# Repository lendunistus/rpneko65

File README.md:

# RPNeko65

**This branch contains the work-in-progress second revision. NOTHING HERE IS CONFIRMED WORKING!**

An open source multi-layout PCB for the [Bakeneko65](https://github.com/kkatano/bakeneko-65)

## Features
- QMK/VIA
- RGB LED under Caps Lock (currently non-functional without modification)
- Large amount of layout support
- C3 Unified Daughterboard
- Support for clip-in stabilizers

## Layout support

## Release history
- Rev 1: Initial prototype. Caps Lock LED is non-functional due to incorrect capacitor wiring, can be fixed by removing the capacitor and bridging the two pads. ANSI enter and spacebar stabiliser holes are also misaligned

## Credits
- kkatano for creating the original Bakeneko65
- Zykrah for their [firmware script](https://github.com/zykrah/firmware-scripts)
- MarvFPV and ebastler for [marbastlib](https://github.com/ebastler/marbastlib)
- Sleepdealer for their [RP2040 design guide](https://github.com/Sleepdealr/RP2040-designguide)
- People in the Keyboard Atelier server for the help and assistance

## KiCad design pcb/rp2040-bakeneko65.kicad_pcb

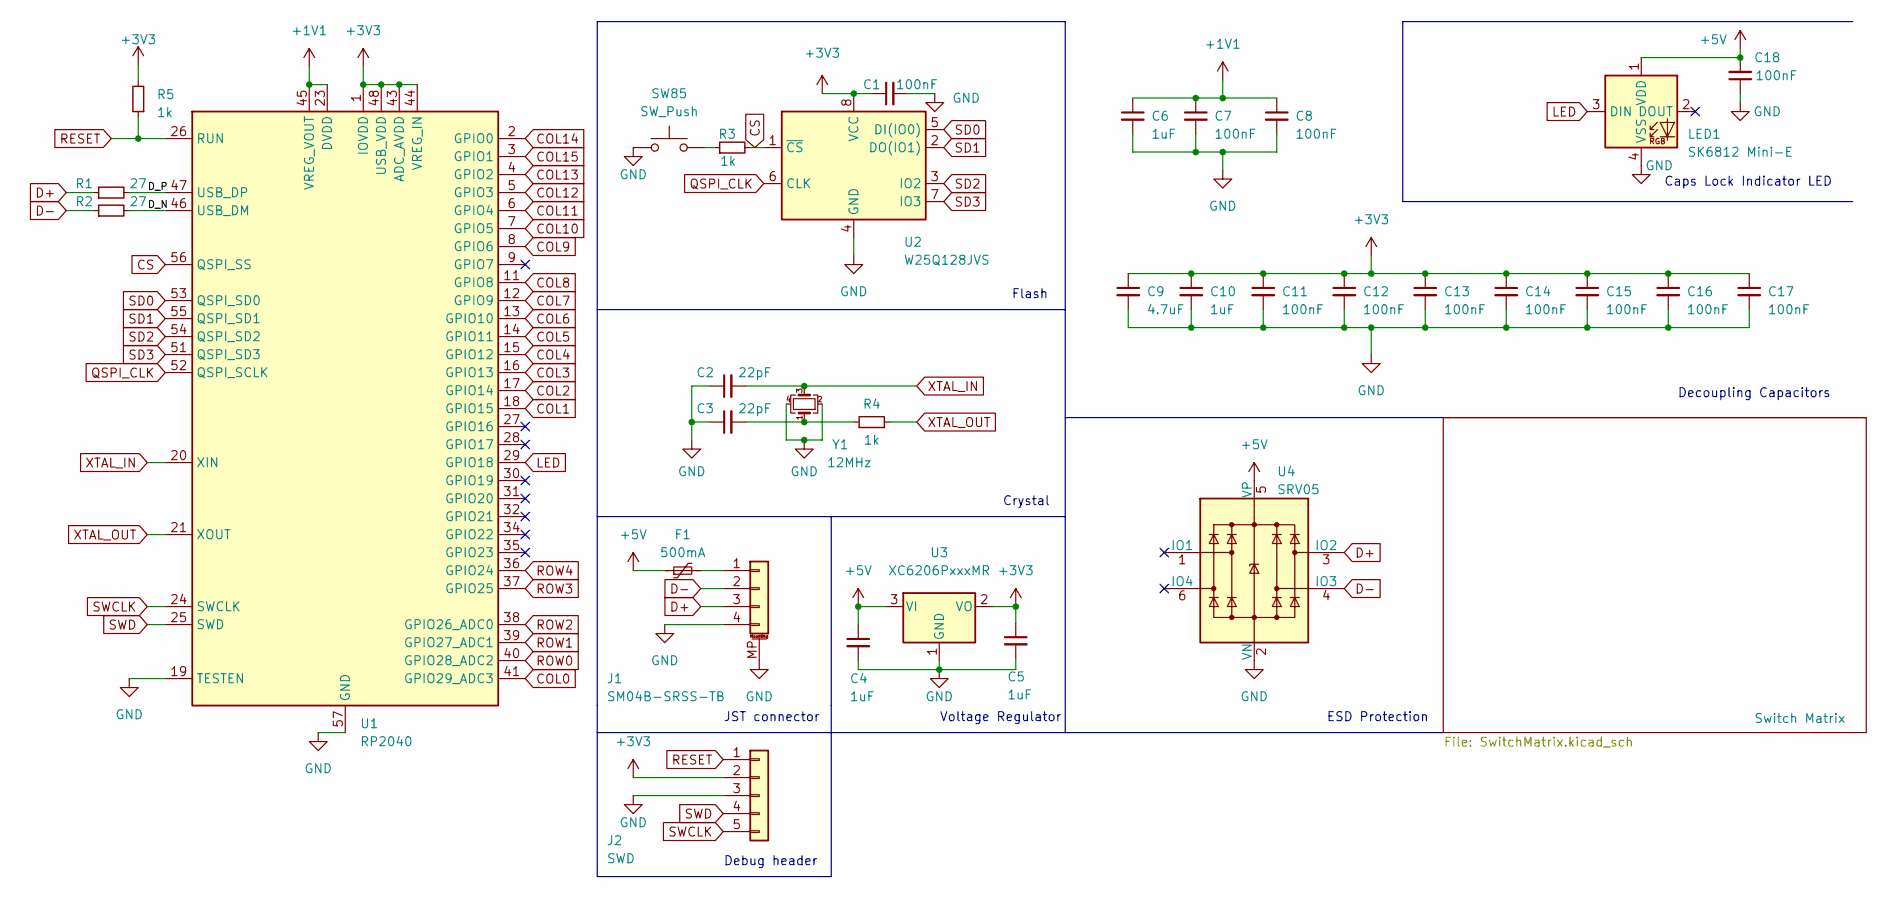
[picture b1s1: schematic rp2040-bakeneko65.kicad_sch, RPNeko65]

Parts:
C1, C7, C8, C11, C12, C13, C14, C15, C16, C17, C18: 100nF; C_0402_1005Metric
C2, C3: 22pF; C_0402_1005Metric
C4, C5, C6, C10: 1uF; C_0402_1005Metric
C9: 4.7uF; C_0402_1005Metric
F1: 500mA; Fuse_1206_3216Metric
J1: SM04B-SRSS-TB; JST_SH_SM04B-SRSS-TB_1x04-1MP_P1.00mm_Horizontal
J2: SWD; PinSocket_1x05_P2.54mm_Vertical
LED1: SK6812 Mini-E; LED_MX_6028R
R1, R2: 27; R_0603_1608Metric
R3, R4, R5: 1k; R_0402_1005Metric
SW85: SW_Push; SW_SPST_SKQG_WithStem
U1: RP2040; QFN-56-1EP_7x7mm_P0.4mm_EP3.2x3.2mm
U2: W25Q128JVS; SOIC-8_5.23x5.23mm_P1.27mm
U3: XC6206PxxxMR; SOT-23
U4: SRV05; SOT-23-6-routable
Y1: 12MHz; Crystal_SMD_3225-4Pin_3.2x2.5mm

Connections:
+1V1: C6.1, C7.1, C8.1, U1.23 (DVDD), U1.45 (VREG_VOUT), U1.50 (DVDD)
+3V3: C1.1, C5.1, C9.1, C10.1, C11.1, C12.1, C13.1, C14.1, C15.1, C16.1, C17.1, J2.2, R5.2, U1.1 (IOVDD), U1.10 (IOVDD), U1.22 (IOVDD), U1.33 (IOVDD), U1.42 (IOVDD), U1.43 (ADC_AVDD), U1.44 (VREG_IN), U1.48 (USB_VDD), U1.49 (IOVDD), U2.8 (VCC), U3.2 (VO)
+5V: C4.1, C18.2, F1.1, LED1.1 (VDD), U3.3 (VI), U4.5 (VP)
/D_N: R2.2, U1.46 (USB_DM)
/D_P: R1.2, U1.47 (USB_DP)
COL0: U1.41 (GPIO29_ADC3); also elsewhere on the board
COL1: U1.18 (GPIO15); also elsewhere on the board
COL2: U1.17 (GPIO14); also elsewhere on the board
COL3: U1.16 (GPIO13); also elsewhere on the board
COL4: U1.15 (GPIO12); also elsewhere on the board
COL5: U1.14 (GPIO11); also elsewhere on the board
COL6: U1.13 (GPIO10); also elsewhere on the board
COL7: U1.12 (GPIO9); also elsewhere on the board
COL8: U1.11 (GPIO8); also elsewhere on the board
COL9: U1.8 (GPIO6); also elsewhere on the board
COL10: U1.7 (GPIO5); also elsewhere on the board
COL11: U1.6 (GPIO4); also elsewhere on the board
COL12: U1.5 (GPIO3); also elsewhere on the board
COL13: U1.4 (GPIO2); also elsewhere on the board
COL14: U1.2 (GPIO0); also elsewhere on the board
COL15: U1.3 (GPIO1); also elsewhere on the board
CS: R3.2, U1.56 (QSPI_SS), U2.1 (~CS)
D+: J1.3, R1.1, U4.3 (IO2)
D-: J1.2, R2.1, U4.4 (IO3)
GND: C1.2, C2.1, C3.1, C4.2, C5.2, C6.2, C7.2, C8.2, C9.2, C10.2, C11.2, C12.2, C13.2, C14.2, C15.2, C16.2, C17.2, C18.1, J1.4, J1.MP (MountPin), J2.3, LED1.4 (VSS), SW85.1, U1.19 (TESTEN), U1.57 (GND), U2.4 (GND), U3.1 (GND), U4.2 (VN), Y1.2, Y1.4
LED: LED1.3 (DIN), U1.29 (GPIO18)
unnamed: C3.2, R4.1, Y1.1
unnamed: F1.2, J1.1
unnamed: R3.1, SW85.2
QSPI_CLK: U1.52 (QSPI_SCLK), U2.6 (CLK)
RESET: J2.1, R5.1, U1.26 (RUN)
ROW0: U1.40 (GPIO28_ADC2); also elsewhere on the board
ROW1: U1.39 (GPIO27_ADC1); also elsewhere on the board
ROW2: U1.38 (GPIO26_ADC0); also elsewhere on the board
ROW3: U1.37 (GPIO25); also elsewhere on the board
ROW4: U1.36 (GPIO24); also elsewhere on the board
SD0: U1.53 (QSPI_SD0), U2.5 (DI(IO0))
SD1: U1.55 (QSPI_SD1), U2.2 (DO(IO1))
SD2: U1.54 (QSPI_SD2), U2.3 (IO2)
SD3: U1.51 (QSPI_SD3), U2.7 (IO3)
SWCLK: J2.5, U1.24 (SWCLK)
SWD: J2.4, U1.25 (SWD)
XTAL_IN: C2.2, U1.20 (XIN), Y1.3
XTAL_OUT: R4.2, U1.21 (XOUT)

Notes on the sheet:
Voltage Regulator
Flash
JST connector
ESD Protection
Crystal
Caps Lock Indicator LED
Decoupling Capacitors
Debug header

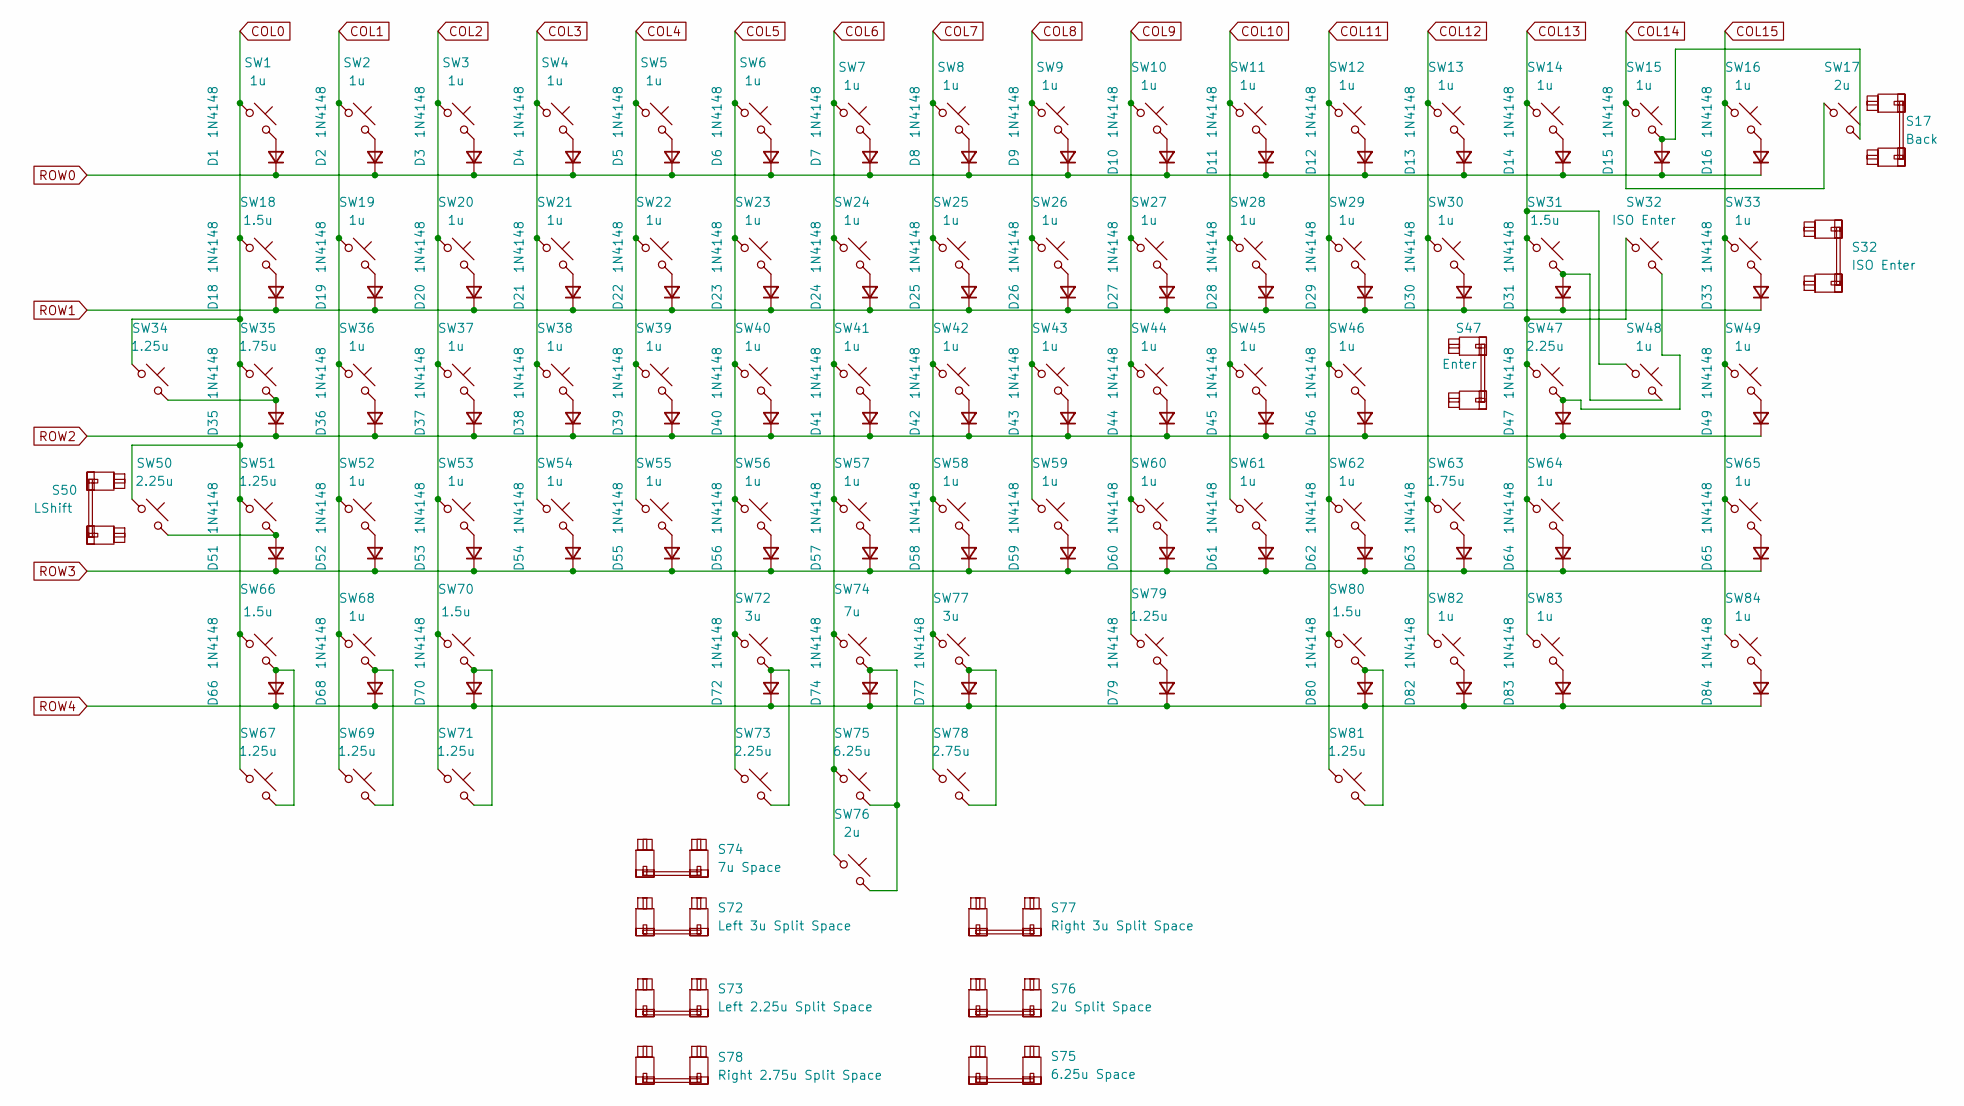
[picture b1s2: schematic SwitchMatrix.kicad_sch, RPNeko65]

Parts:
D1, D2, D3, D4, D5, D6, D7, D8, D9, D10, D11, D12, D13, D14, D15, D16, D18, D19, D20, D21, D22, D23, D24, D25, D26, D27, D28, D29, D30, D31, D33, D35, D36, D37, D38, D39, D40, D41, D42, D43, D44, D45, D46, D47, D49, D51, D52, D53, D54, D55, D56, D57, D58, D59, D60, D61, D62, D63, D64, D65, D66, D68, D70, D72, D74, D77, D79, D80, D82, D83, D84: 1N4148; D_SOD-123
S17: Back; STAB_MX_P_2u
S32: ISO Enter; STAB_MX_P_ISO
S47: Enter; STAB_MX_P_2.25u
S50: LShift; STAB_MX_P_2.25u
S72: Left 3u Split Space; STAB_MX_P_3u
S73: Left 2.25u Split Space; STAB_MX_P_2.25u
S74: 7u Space; STAB_MX_P_7u
S75: 6.25u Space; STAB_MX_P_6.25u
S76: 2u Split Space; STAB_MX_P_2u
S77: Right 3u Split Space; STAB_MX_P_3u
S78: Right 2.75u Split Space; STAB_MX_P_2.75u
SW1, SW2, SW3, SW4, SW5, SW6, SW7, SW8, SW9, SW10, SW11, SW12, SW13, SW14, SW15, SW16, SW19, SW20, SW21, SW22, SW23, SW24, SW25, SW26, SW27, SW28, SW29, SW30, SW33, SW36, SW37, SW38, SW39, SW40, SW41, SW42, SW43, SW44, SW45, SW46, SW48, SW49, SW52, SW53, SW54, SW55, SW56, SW57, SW58, SW59, SW60, SW61, SW62, SW64, SW65, SW68, SW82, SW83, SW84: 1u; SW_MX_1u
SW17, SW76: 2u; SW_MX_1u
SW18, SW31, SW66, SW70, SW80: 1.5u; SW_MX_1.5u
SW32: ISO Enter; SW_MX_1u
SW34, SW51, SW67, SW69, SW71, SW79, SW81: 1.25u; SW_MX_1.25u
SW35, SW63: 1.75u; SW_MX_1.75u
SW47, SW50, SW73: 2.25u; SW_MX_1u
SW72, SW77: 3u; SW_MX_1u
SW74: 7u; SW_MX_1u
SW75: 6.25u; SW_MX_1u
SW78: 2.75u; SW_MX_1u

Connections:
COL0: SW1.1, SW18.1, SW34.1, SW35.1, SW50.1, SW51.1, SW66.1, SW67.1; also elsewhere on the board
COL1: SW2.1, SW19.1, SW36.1, SW52.1, SW68.1, SW69.1; also elsewhere on the board
COL2: SW3.1, SW20.1, SW37.1, SW53.1, SW70.1, SW71.1; also elsewhere on the board
COL3: SW4.1, SW21.1, SW38.1, SW54.1; also elsewhere on the board
COL4: SW5.1, SW22.1, SW39.1, SW55.1; also elsewhere on the board
COL5: SW6.1, SW23.1, SW40.1, SW56.1, SW72.1, SW73.1; also elsewhere on the board
COL6: SW7.1, SW24.1, SW41.1, SW57.1, SW74.1, SW75.1, SW76.1; also elsewhere on the board
COL7: SW8.1, SW25.1, SW42.1, SW58.1, SW77.1, SW78.1; also elsewhere on the board
COL8: SW9.1, SW26.1, SW43.1, SW59.1; also elsewhere on the board
COL9: SW10.1, SW27.1, SW44.1, SW60.1, SW79.1; also elsewhere on the board
COL10: SW11.1, SW28.1, SW45.1, SW61.1; also elsewhere on the board
COL11: SW12.1, SW29.1, SW46.1, SW62.1, SW80.1, SW81.1; also elsewhere on the board
COL12: SW13.1, SW30.1, SW63.1, SW82.1; also elsewhere on the board
COL13: SW14.1, SW31.1, SW32.1, SW47.1, SW48.1, SW64.1, SW83.1; also elsewhere on the board
COL14: SW15.1, SW17.1; also elsewhere on the board
COL15: SW16.1, SW33.1, SW49.1, SW65.1, SW84.1; also elsewhere on the board
unnamed: D1.2 (A), SW1.2
unnamed: D2.2 (A), SW2.2
unnamed: D3.2 (A), SW3.2
unnamed: D4.2 (A), SW4.2
unnamed: D5.2 (A), SW5.2
unnamed: D6.2 (A), SW6.2
unnamed: D7.2 (A), SW7.2
unnamed: D8.2 (A), SW8.2
unnamed: D9.2 (A), SW9.2
unnamed: D10.2 (A), SW10.2
unnamed: D11.2 (A), SW11.2
unnamed: D12.2 (A), SW12.2
unnamed: D13.2 (A), SW13.2
unnamed: D14.2 (A), SW14.2
unnamed: D15.2 (A), SW15.2, SW17.2
unnamed: D16.2 (A), SW16.2
unnamed: D18.2 (A), SW18.2
unnamed: D19.2 (A), SW19.2
unnamed: D20.2 (A), SW20.2
unnamed: D21.2 (A), SW21.2
unnamed: D22.2 (A), SW22.2
unnamed: D23.2 (A), SW23.2
unnamed: D24.2 (A), SW24.2
unnamed: D25.2 (A), SW25.2
unnamed: D26.2 (A), SW26.2
unnamed: D27.2 (A), SW27.2
unnamed: D28.2 (A), SW28.2
unnamed: D29.2 (A), SW29.2
unnamed: D30.2 (A), SW30.2
unnamed: D31.2 (A), SW31.2, SW48.2
unnamed: D33.2 (A), SW33.2
unnamed: D35.2 (A), SW34.2, SW35.2
unnamed: D36.2 (A), SW36.2
unnamed: D37.2 (A), SW37.2
unnamed: D38.2 (A), SW38.2
unnamed: D39.2 (A), SW39.2
unnamed: D40.2 (A), SW40.2
unnamed: D41.2 (A), SW41.2
unnamed: D42.2 (A), SW42.2
unnamed: D43.2 (A), SW43.2
unnamed: D44.2 (A), SW44.2
unnamed: D45.2 (A), SW45.2
unnamed: D46.2 (A), SW46.2
unnamed: D47.2 (A), SW32.2, SW47.2
unnamed: D49.2 (A), SW49.2
unnamed: D51.2 (A), SW50.2, SW51.2
unnamed: D52.2 (A), SW52.2
unnamed: D53.2 (A), SW53.2
unnamed: D54.2 (A), SW54.2
unnamed: D55.2 (A), SW55.2
unnamed: D56.2 (A), SW56.2
unnamed: D57.2 (A), SW57.2
unnamed: D58.2 (A), SW58.2
unnamed: D59.2 (A), SW59.2
unnamed: D60.2 (A), SW60.2
unnamed: D61.2 (A), SW61.2
unnamed: D62.2 (A), SW62.2
unnamed: D63.2 (A), SW63.2
unnamed: D64.2 (A), SW64.2
unnamed: D65.2 (A), SW65.2
unnamed: D66.2 (A), SW66.2, SW67.2
unnamed: D68.2 (A), SW68.2, SW69.2
unnamed: D70.2 (A), SW70.2, SW71.2
unnamed: D72.2 (A), SW72.2, SW73.2
unnamed: D74.2 (A), SW74.2, SW75.2, SW76.2
unnamed: D77.2 (A), SW77.2, SW78.2
unnamed: D79.2 (A), SW79.2
unnamed: D80.2 (A), SW80.2, SW81.2
unnamed: D82.2 (A), SW82.2
unnamed: D83.2 (A), SW83.2
unnamed: D84.2 (A), SW84.2
ROW0: D1.1 (K), D2.1 (K), D3.1 (K), D4.1 (K), D5.1 (K), D6.1 (K), D7.1 (K), D8.1 (K), D9.1 (K), D10.1 (K), D11.1 (K), D12.1 (K), D13.1 (K), D14.1 (K), D15.1 (K), D16.1 (K); also elsewhere on the board
ROW1: D18.1 (K), D19.1 (K), D20.1 (K), D21.1 (K), D22.1 (K), D23.1 (K), D24.1 (K), D25.1 (K), D26.1 (K), D27.1 (K), D28.1 (K), D29.1 (K), D30.1 (K), D31.1 (K), D33.1 (K); also elsewhere on the board
ROW2: D35.1 (K), D36.1 (K), D37.1 (K), D38.1 (K), D39.1 (K), D40.1 (K), D41.1 (K), D42.1 (K), D43.1 (K), D44.1 (K), D45.1 (K), D46.1 (K), D47.1 (K), D49.1 (K); also elsewhere on the board
ROW3: D51.1 (K), D52.1 (K), D53.1 (K), D54.1 (K), D55.1 (K), D56.1 (K), D57.1 (K), D58.1 (K), D59.1 (K), D60.1 (K), D61.1 (K), D62.1 (K), D63.1 (K), D64.1 (K), D65.1 (K); also elsewhere on the board
ROW4: D66.1 (K), D68.1 (K), D70.1 (K), D72.1 (K), D74.1 (K), D77.1 (K), D79.1 (K), D80.1 (K), D82.1 (K), D83.1 (K), D84.1 (K); also elsewhere on the board

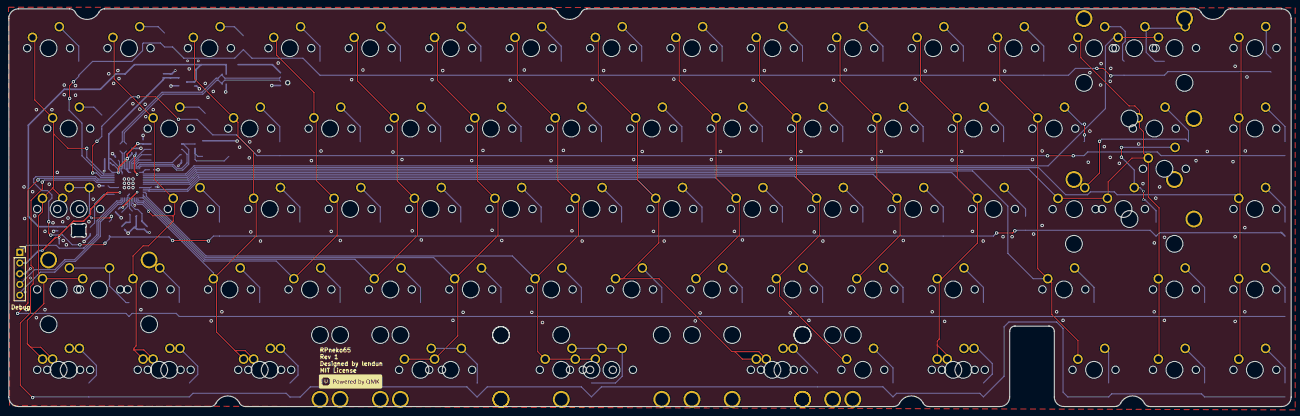
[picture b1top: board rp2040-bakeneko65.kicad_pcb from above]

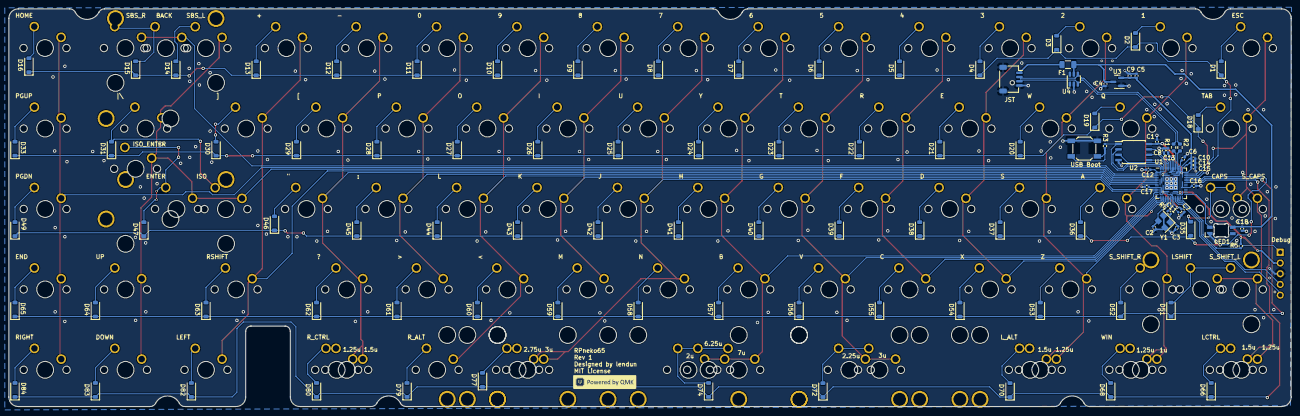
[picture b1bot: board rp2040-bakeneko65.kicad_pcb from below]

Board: 2 copper layers, 303.8 x 94.2 mm, 199 parts (103 on the bottom side), 115 nets.

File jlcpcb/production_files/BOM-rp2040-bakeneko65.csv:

Comment,Designator,Footprint,LCSC
1k,"R3,R4,R5",R_0402_1005Metric,C11702
500mA,F1,Fuse_1206_3216Metric,C151162
22pF,"C2,C3",C_0402_1005Metric,C1555
SM04B-SRSS-TB,J1,JST_SH_SM04B-SRSS-TB_1x04-1MP_P1.00mm_Horizontal,C160404
RP2040,U1,QFN-56-1EP_7x7mm_P0.4mm_EP3.2x3.2mm,C2040
4.7uF,C9,C_0402_1005Metric,C23733
27,"R1,R2",R_0603_1608Metric,C25190
100nF,"C1,C11,C12,C13,C14,C15,C16,C17,C18,C7,C8",C_0402_1005Metric,C307331
SW_Push,SW85,SW_SPST_SKQG_WithStem,C318884
SK6812 Mini-E,LED1,LED_MX_6028R,C524051
1uF,"C10,C4,C5,C6",C_0402_1005Metric,C52923
XC6206PxxxMR,U3,SOT-23,C5446
1N4148,"D1,D10,D11,D12,D13,D14,D15,D16,D18,D19,D2,D20,D21,D22,D23,D24,D25,D26,D27,D28,D29,D3,D30,D31,D33,D35,D36,D37,D38,D39,D4,D40,D41,D42,D43,D44,D45,D46,D47,D49,D5,D51,D52,D53,D54,D55,D56,D57,D58,D59,D6,D60,D61,D62,D63,D64,D65,D66,D68,D7,D70,D72,D74,D77,D79,D8,D80,D82,D83,D84,D9",D_SOD-123,C81598
SRV05,U4,SOT-23-6-routable,C85364
12MHz,Y1,Crystal_SMD_3225-4Pin_3.2x2.5mm,C9002
W25Q128JVS,U2,SOIC-8_5.23x5.23mm_P1.27mm,C97521

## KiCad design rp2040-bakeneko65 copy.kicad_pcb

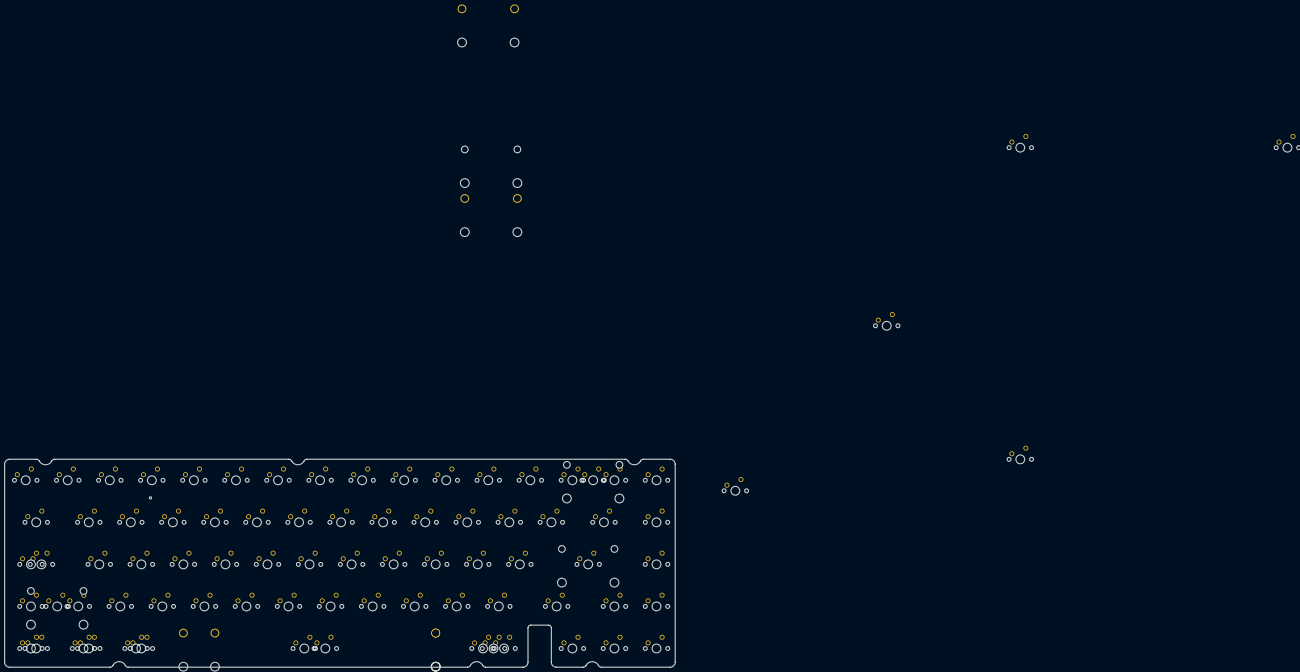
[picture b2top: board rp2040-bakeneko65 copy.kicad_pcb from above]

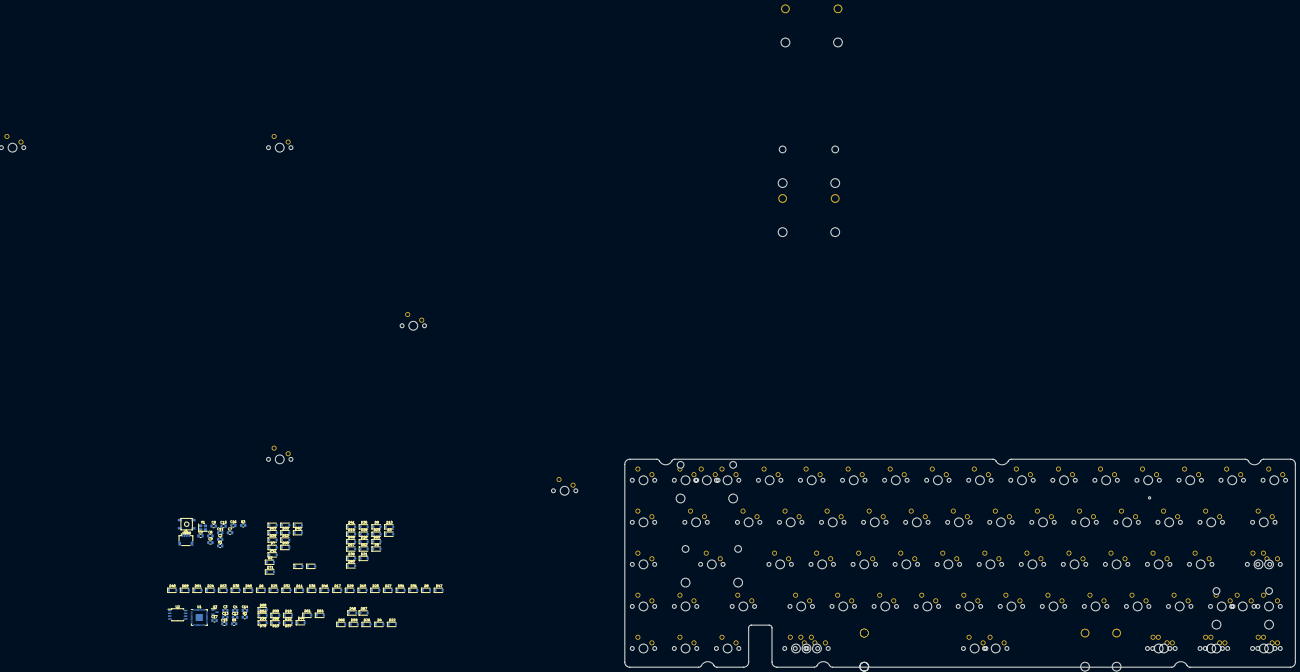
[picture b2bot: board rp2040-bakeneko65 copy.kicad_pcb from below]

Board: 2 copper layers, 303.8 x 94.2 mm, 187 parts (97 on the bottom side), 110 nets, no tracks yet.

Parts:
C2, C3: 22pF; C_0805_2012Metric
C4, C5, C6, C10: 1uF; C_0805_2012Metric
C7, C8, C11, C12, C13, C14, C15, C16, C17: 100nF; C_0805_2012Metric
C9: 10uF; C_0805_2012Metric
D1, D2, D3, D4, D5, D6, D7, D8, D9, D10, D11, D12, D13, D14, D15, D16, D17, D18, D19, D20, D21, D22, D23, D24, D25, D26, D27, D28, D29, D30, D31, D32, D33, D34, D35, D36, D37, D38, D39, D40, D41, D42, D43, D44, D45, D46, D47, D48, D49, D50, D51, D52, D53, D54, D55, D56, D57, D58, D59, D60, D61, D62, D63, D64, D65, D66, D67, D68, D69, D70, D71: 1N4148; D_SOD-123
J1: SM04B-SRSS-TB; JST_SH_SM04B-SRSS-TB_1x04-1MP_P1.00mm_Horizontal
R1, R2: 27; R_0805_2012Metric
R3: 10k; R_0805_2012Metric
R4: 1k; R_0805_2012Metric
S1: Back; STAB_MX_2u
S2: LShift; STAB_MX_2u
S3: ISO Enter; STAB_MX_2u
S4: 7u Space; STAB_MX_P_7u
S5: 6.25u Space; STAB_MX_P_6.25u
S6: Left Split Space; STAB_MX_P_2u
S7: Right Split Space; STAB_MX_P_2u
S8: Enter; STAB_MX_2u
SW1, SW2, SW3, SW4, SW5, SW6, SW7, SW8, SW9, SW10, SW11, SW12, SW13, SW14, SW15, SW16, SW19, SW20, SW21, SW22, SW23, SW24, SW25, SW26, SW27, SW28, SW29, SW30, SW33, SW36, SW37, SW38, SW39, SW40, SW41, SW42, SW43, SW44, SW45, SW46, SW48, SW49, SW52, SW53, SW54, SW55, SW56, SW57, SW58, SW59, SW60, SW61, SW62, SW64, SW65, SW67, SW72, SW73, SW74, SW82: 1u; SW_MX_1u
SW17: 2u; SW_MX_1u
SW18, SW31, SW66, SW68, SW71: 1.5u; SW_MX_1u
SW32: ISO Enter; SW_MX_1u
SW34, SW51, SW70, SW75, SW76, SW77, SW79: 1.25u; SW_MX_1u
SW35, SW63: 1.75u; SW_MX_1u
SW47, SW50: 2.25u; SW_MX_1u
SW69: 7u; SW_MX_1u
SW78: 6.25u; SW_MX_1u
SW80: SW_Push; SKQG-1155865
SW81, SW83: 3u; SW_MX_1u
U1: RP2040; QFN-56-1EP_7x7mm_P0.4mm_EP3.2x3.2mm
U2: W25Q128JVS; SOIC-8_5.23x5.23mm_P1.27mm
U3: XC6206PxxxMR; SOT-23
Y1: 12MHz; Crystal_SMD_3225-4Pin_3.2x2.5mm

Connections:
+1V1: C6.1, C7.1, C8.1, U1.23 (DVDD), U1.45 (VREG_VOUT), U1.50 (DVDD)
+3V3: C5.1, C9.1, C10.1, C11.1, C12.1, C13.1, C14.1, C15.1, C16.1, C17.1, R3.1, U1.1 (IOVDD), U1.10 (IOVDD), U1.22 (IOVDD), U1.33 (IOVDD), U1.42 (IOVDD), U1.43 (ADC_AVDD), U1.44 (VREG_IN), U1.48 (USB_VDD), U1.49 (IOVDD), U2.8 (VCC), U3.2 (VO)
+5V: C4.1, J1.1, U3.3 (VI)
COL0: SW1.1, SW18.1, SW34.1, SW35.1, SW50.1, SW51.1, SW66.1, SW75.1
COL1: SW2.1, SW19.1, SW36.1, SW52.1, SW67.1, SW76.1
COL2: SW3.1, SW20.1, SW37.1, SW53.1, SW68.1, SW77.1
COL3: SW4.1, SW21.1, SW38.1, SW54.1
COL4: SW5.1, SW22.1, SW39.1, SW55.1
COL5: SW6.1, SW23.1, SW40.1, SW56.1, SW81.1
COL6: SW7.1, SW24.1, SW41.1, SW57.1, SW69.1, SW78.1, SW82.1
COL7: SW8.1, SW25.1, SW42.1, SW58.1, SW83.1
COL8: SW9.1, SW26.1, SW43.1, SW59.1
COL9: SW10.1, SW27.1, SW44.1, SW60.1, SW70.1
COL10: SW11.1, SW28.1, SW45.1, SW61.1
COL11: SW12.1, SW29.1, SW46.1, SW62.1, SW71.1, SW79.1
COL12: SW13.1, SW30.1, SW63.1, SW72.1
COL13: SW14.1, SW31.1, SW32.1, SW47.1, SW48.1, SW64.1, SW73.1
COL14: SW15.1, SW17.1
COL15: SW16.1, SW33.1, SW49.1, SW65.1, SW74.1
CS: U1.56 (QSPI_SS), U2.1 (~CS)
D+: J1.2, R1.1
D-: J1.3, R2.1
GND: C2.1, C3.1, C4.2, C5.2, C6.2, C7.2, C8.2, C9.2, C10.2, C11.2, C12.2, C13.2, C14.2, C15.2, C16.2, C17.2, J1.4, J1.MP (MountPin), SW80.1, U1.19 (TESTEN), U1.57 (GND), U2.4 (GND), U3.1 (GND), Y1.2, Y1.4
unnamed: C3.2, R4.1, Y1.1
unnamed: D1.2 (A), SW1.2
unnamed: D2.2 (A), SW2.2
unnamed: D3.2 (A), SW3.2
unnamed: D4.2 (A), SW4.2
unnamed: D5.2 (A), SW5.2
unnamed: D6.2 (A), SW6.2
unnamed: D7.2 (A), SW7.2
unnamed: D8.2 (A), SW8.2
unnamed: D9.2 (A), SW9.2
unnamed: D10.2 (A), SW10.2
unnamed: D11.2 (A), SW11.2
unnamed: D12.2 (A), SW12.2
unnamed: D13.2 (A), SW13.2
unnamed: D14.2 (A), SW14.2
unnamed: D15.2 (A), SW15.2, SW17.2
unnamed: D16.2 (A), SW16.2
unnamed: D17.2 (A), SW18.2
unnamed: D18.2 (A), SW19.2
unnamed: D19.2 (A), SW20.2
unnamed: D20.2 (A), SW21.2
unnamed: D21.2 (A), SW22.2
unnamed: D22.2 (A), SW23.2
unnamed: D23.2 (A), SW24.2
unnamed: D24.2 (A), SW25.2
unnamed: D25.2 (A), SW26.2
unnamed: D26.2 (A), SW27.2
unnamed: D27.2 (A), SW28.2
unnamed: D28.2 (A), SW29.2
unnamed: D29.2 (A), SW30.2
unnamed: D30.2 (A), SW31.2, SW48.2
unnamed: D31.2 (A), SW33.2
unnamed: D32.2 (A), SW34.2, SW35.2
unnamed: D33.2 (A), SW36.2
unnamed: D34.2 (A), SW37.2
unnamed: D35.2 (A), SW38.2
unnamed: D36.2 (A), SW39.2
unnamed: D37.2 (A), SW40.2
unnamed: D38.2 (A), SW41.2
unnamed: D39.2 (A), SW42.2
unnamed: D40.2 (A), SW43.2
unnamed: D41.2 (A), SW44.2
unnamed: D42.2 (A), SW45.2
unnamed: D43.2 (A), SW46.2
unnamed: D44.2 (A), SW32.2, SW47.2
unnamed: D45.2 (A), SW49.2
unnamed: D46.2 (A), SW50.2, SW51.2
unnamed: D47.2 (A), SW52.2
unnamed: D48.2 (A), SW53.2
unnamed: D49.2 (A), SW54.2
unnamed: D50.2 (A), SW55.2
unnamed: D51.2 (A), SW56.2
unnamed: D52.2 (A), SW57.2
unnamed: D53.2 (A), SW58.2
unnamed: D54.2 (A), SW59.2
unnamed: D55.2 (A), SW60.2
unnamed: D56.2 (A), SW61.2
unnamed: D57.2 (A), SW62.2
unnamed: D58.2 (A), SW63.2
unnamed: D59.2 (A), SW64.2
unnamed: D60.2 (A), SW65.2
unnamed: D61.2 (A), SW66.2, SW75.2
unnamed: D62.2 (A), SW67.2, SW76.2
unnamed: D63.2 (A), SW68.2, SW77.2
unnamed: D64.2 (A), SW69.2, SW78.2, SW82.2
unnamed: D65.2 (A), SW70.2
unnamed: D66.2 (A), SW71.2, SW79.2
unnamed: D67.2 (A), SW72.2
unnamed: D68.2 (A), SW73.2
unnamed: D69.2 (A), SW74.2
unnamed: D70.2 (A), SW81.2
unnamed: D71.2 (A), SW83.2
unnamed: R1.2, U1.47 (USB_DP)
unnamed: R2.2, U1.46 (USB_DM)
unnamed: R3.2, SW80.2, U1.26 (RUN)
QSPI_CLK: U1.52 (QSPI_SCLK), U2.6 (CLK)
ROW0: D1.1 (K), D2.1 (K), D3.1 (K), D4.1 (K), D5.1 (K), D6.1 (K), D7.1 (K), D8.1 (K), D9.1 (K), D10.1 (K), D11.1 (K), D12.1 (K), D13.1 (K), D14.1 (K), D15.1 (K), D16.1 (K)
ROW1: D17.1 (K), D18.1 (K), D19.1 (K), D20.1 (K), D21.1 (K), D22.1 (K), D23.1 (K), D24.1 (K), D25.1 (K), D26.1 (K), D27.1 (K), D28.1 (K), D29.1 (K), D30.1 (K), D31.1 (K)
ROW2: D32.1 (K), D33.1 (K), D34.1 (K), D35.1 (K), D36.1 (K), D37.1 (K), D38.1 (K), D39.1 (K), D40.1 (K), D41.1 (K), D42.1 (K), D43.1 (K), D44.1 (K), D45.1 (K)
ROW3: D46.1 (K), D47.1 (K), D48.1 (K), D49.1 (K), D50.1 (K), D51.1 (K), D52.1 (K), D53.1 (K), D54.1 (K), D55.1 (K), D56.1 (K), D57.1 (K), D58.1 (K), D59.1 (K), D60.1 (K)
ROW4: D61.1 (K), D62.1 (K), D63.1 (K), D64.1 (K), D65.1 (K), D66.1 (K), D67.1 (K), D68.1 (K), D69.1 (K), D70.1 (K), D71.1 (K)
SD0: U1.53 (QSPI_SD0), U2.5 (DI(IO0))
SD1: U1.55 (QSPI_SD1), U2.2 (DO(IO1))
SD2: U1.54 (QSPI_SD2), U2.3 (IO2)
SD3: U1.51 (QSPI_SD3), U2.7 (IO3)
XTAL_IN: C2.2, U1.20 (XIN), Y1.3
XTAL_OUT: R4.2, U1.21 (XOUT)

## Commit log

2022-11-10 Add some stuff
2022-11-10 Some schematic work
2022-11-10 MCU done
2022-11-11 Add flash
2022-11-11 Add crystal
2022-11-11 Some line stuff
2022-11-12 Add ai03 lib
2022-11-12 JST and voltage regulator
2022-11-12 Add decoupling capacitors
2022-11-12 Add subsheet
2022-11-12 Some matrix stuff
2022-11-12 Some stuff
2022-11-13 Add ai03 lib to project file
2022-11-13 Some matrix work
2022-11-13 Some more matrix stuff
2022-11-13 Columns
2022-11-15 ISO + some wiring
2022-11-15 Rows
2022-11-15 Label switches and diodes
2022-11-15 Split space
2022-11-15 Fixed split space routing
2022-11-15 idek
2022-11-15 Assign footprints
2022-11-15 Initialize PCB
2022-11-16 Add outline
2022-11-16 A couple switches
2022-11-16 Some more switches
2022-11-17 Move switches a bit
2022-11-17 Even more switches
2022-11-17 Add stabs
2022-11-17 Correct stabs
2022-11-17 oops, forgot ANSI enter
2022-11-17 Position a couple stabs
2022-11-17 Switches galore
2022-11-18 Add KLE
2022-11-19 Attempt to use autoplacer plugin
2022-11-19 even more desperate attempts at autopicker
2022-11-19 Finally got the keys and diodes placed
2022-11-19 oops, messed up a couple stabs
2022-11-19 Some routing
2022-11-19 Routing stuff
2022-11-19 Column routing semi-done
2022-11-19 Failed attempt to route MCU traces
2022-11-19 figured out MCU traces
2022-11-20 screw MCU routing
2022-11-20 Ground vias
2022-11-20 Reposition MCU
2022-11-23 couple more things
2022-11-26 some more dumpster fire routing
2022-11-28 Some decoupling caps
2022-12-02 starting over on MCU routing
2022-12-03 Use smaller caps and resistors
2022-12-04 Reposition crystal
2022-12-07 Complete crystal
2022-12-07 failed attempt to route USB DP/DN
2022-12-08 some JST stuff
2022-12-08 Power and some decoupling caps
2022-12-08 Flash
2022-12-10 some stuff to prepare for fill zones
2022-12-10 some net nonsense
2022-12-11 3V3 fill
2022-12-11 Some ground fills
2022-12-15 Starting over on routing
2022-12-15 Add ESD protection
2022-12-16 Polyfuse and 2u split space
2022-12-18 Add caps lock LED symbol
2022-12-18 Assign footprints (again)
2022-12-18 The first switch (again)
2022-12-19 Update KLE's
2022-12-19 Place switches (with broken stabs)
2022-12-19 forgot to save PCB
2022-12-19 Attempt to get stabs to work
2022-12-19 Add stabfix KLE
2022-12-26 second (unsuccessful) attempt to fix stabs
2022-12-26 third unsuccessful stab fix
2023-01-24 Use ghost keys to fix stabs (thanks zykrah)
2023-01-26 Add debug header to schematic
2023-03-24 Assign footprints, add knob symbol
2023-03-24 some complete mess with the reset button idk
2023-04-01 replacing MCU, some col traces
2023-04-01 Some extra routing
2023-04-02 actually place encoder correctly
2023-04-03 Route debug header
2023-04-04 A couple decoupling caps
2023-04-05 (poorly) route JST
2023-04-06 Add voltage regulator
2023-04-07 get started on flash
2023-04-07 flash, redo ESD, some other stuff
2023-04-07 USB boot
2023-04-07 add caps lock LED (also route SRV05 properly)
2023-04-07 LED + decoupling caps + a lot of stuff
2023-04-08 reposition flash
2023-04-08 (poorly) route debug header
2023-04-08 incomplete attempt at routing power
2023-04-08 some more power progress
2023-04-08 column routing
2023-04-08 col routing sucked too much
2023-04-08 reposition MCU (again)
2023-04-08 more col routing
2023-04-09 Revert "more col routing"
    This reverts commit cb50b5119402ddcb1d4d4028dc95a6a712835f21.
2023-04-09 MCU reposition + a couple cols
2023-04-09 one more column
2023-04-09 all cols done
2023-04-09 row routing (not into MCU)
2023-04-09 really ugly MCU row routing
2023-04-09 oops, forgot some stuff
2023-04-09 one more diode connection
2023-04-09 oops, have to connect col0 as well
2023-04-09 wire knob to MCU in schematic (+ a GND via)
2023-04-15 add initial plate file
2023-04-15 dot some ground vias around
2023-04-15 some DRC stuff
2023-04-15 screw the knob (+ a couple minor changes)
2023-04-16 JLC tools + C9 needed a bigger footprint
2023-04-16 oops, forgot to actually commit bigger footprint
2023-04-16 some BOM stuff
2023-04-16 remove switches from BOM
2023-04-16 BOM mostly done
2023-04-16 make fuse smaller
2023-04-16 add fuse to BOM
2023-04-16 production files
2023-04-16 some other gerber modification
2023-04-16 clean up a couple row traces
2023-04-17 spaghetti moment
2023-04-18 changing to a 4.7uF bulk cap
2023-04-18 some production files
2023-04-18 change bulk cap to 0402 again
2023-04-19 swap to PCM footprints
2023-04-19 oops, forgot to update LED
2023-04-19 failed attempt at making a plate with kicad
2023-04-19 an attempt to generate plate dxf files
2023-04-19 some progress on plate cleanup
2023-04-22 keebio plate files
2023-04-22 some keebio plate tweaking
2023-04-22 add blocker to plate
2023-04-22 some filleting stuff
2023-04-22 attempt to use qcad
2023-04-23 some component reference placement
2023-04-23 halfway through labelling keys
2023-04-23 just a bit of bottom row to go
2023-04-28 plate maybe finalised
    I just copy pasted the outline from the bakeneko65 plate lmao
2023-05-02 text + routing some traces away from holes
2023-05-02 Debug text
2023-05-02 misc improvements + new gerbers
    debug text, no connection flags on unused GPIOs, etc
2023-05-06 swap out terminating resistors for 0603
2023-05-06 new resistor in BOM
2023-05-06 new production files
2023-05-06 gerbers + some tweaks to resistor placement
2023-05-06 new new gerbers
2023-05-06 move a couple text things
2023-05-06 new new new gerbers
2023-05-06 new JLC files
2023-05-06 increase via size
2023-05-12 fr4 plate
2023-05-12 fix via clearance issues
2023-05-13 new new new new production files
2023-05-14 branding
2023-05-15 branding on the front as well
2023-05-15 semi-final production files
2023-05-15 moved COL traces around a bit
    also fixed C6 text positioning
2023-05-16 finalize COL traces + some other tweaks
2023-05-18 fix crystal routing, sprinkle stitching vias around, etc
    also move some traces around
2023-05-18 move Y1 text
2023-05-19 swap fuse to 1206 (again)
    accidentally mistook a ferrite bead for a fuse when I changed the fuse footprint to 0805, back to 1206 we go
2023-05-19 new production files x5
2023-05-21 adding info to title block
    plus plate file rename
2023-05-21 moved a trace away
2023-05-23 slightly relieve via pox
2023-05-27 move crystal a bit to the left
2023-05-28 change ESD protection pins
2023-06-02 update footprints + delete leftover tracks
2023-06-18 even newer production files
2023-06-22 very small changes
2023-06-22 quite a few changes
    fix switch routing, update footprints, couple other minor tweaks
2023-06-22 fix capacitor alignment
2023-06-23 hopefully final production files
    and a "fixed" plate (turns out the plate didn't need fixing)
2023-06-24 forgot to generate new JLC files
2023-06-25 even newer production files because I'm paranoid
    also the ones I ordered my proto with
2023-06-29 stuff for the firmware script
2023-06-30 working firmware script KLE
2023-07-22 add VIA json
2023-07-25 basic readme
2023-08-13 revised firmware script KLE
2023-08-13 assigning 3D models
2023-08-13 add PCB image to readme
    also add a not working firmware script KLE
2023-08-13 Purple PCB image
2023-08-16 VIA script KLE, fixed VIA json
2023-10-13 add full QMK firmware
2023-10-13 purge unneeded submodules
2023-10-13 remove reference bakeneko, organise repository
2023-10-13 readme clarification
2023-10-13 readme warning
2023-10-13 rev2 readme warning
2023-10-13 fix ANSI enter
2023-10-13 remove non-PCM libraries
2023-10-13 fix LED capacitor (and update footprints)
    and add a missing trace to D47

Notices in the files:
pcb/SwitchMatrix.kicad_sch:
MIT License
